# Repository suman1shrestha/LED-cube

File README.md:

# LED-cube
Led cube using 555-timer

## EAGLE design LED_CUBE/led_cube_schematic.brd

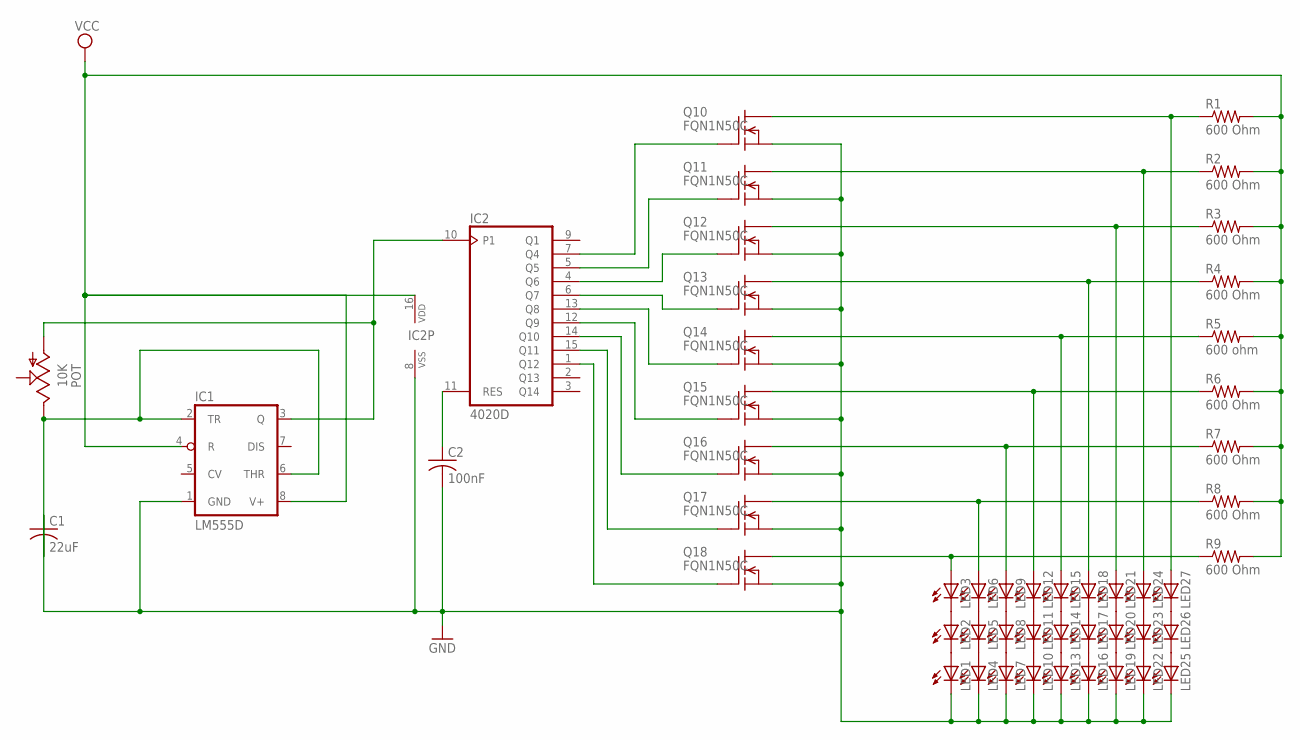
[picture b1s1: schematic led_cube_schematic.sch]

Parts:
C1: 22uF; C075-032X103
C2: 100nF; C075-032X103
IC1: LM555D; SO08
IC2: 4020D; SO16
LED1, LED2, LED3, LED4, LED5, LED6, LED7, LED8, LED9, LED10, LED11, LED12, LED13, LED14, LED15, LED16, LED17, LED18, LED19, LED20, LED21, LED22, LED23, LED24, LED25, LED26, LED27: LEDB155; Q62902-B155
POT: 10K; LI15
Q10, Q11, Q12, Q13, Q14, Q15, Q16, Q17, Q18: FQN1N50C; TO92
R1, R2, R3, R4, R6, R7, R8, R9: 600 Ohm; 0309/12
R5: 600 ohm; 0309/12

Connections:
GND: C1.1, C2.2, IC1.1 (GND), IC2.8 (VSS), LED1.K (C), LED4.K (C), LED7.K (C), LED10.K (C), LED13.K (C), LED16.K (C), LED19.K (C), LED22.K (C), LED25.K (C), Q10.3 (S), Q11.3 (S), Q12.3 (S), Q13.3 (S), Q14.3 (S), Q15.3 (S), Q16.3 (S), Q17.3 (S), Q18.3 (S)
unnamed: C1.2, IC1.2 (TR), IC1.6 (THR), POT.E
unnamed: IC2.1 (Q12), Q18.1 (G)
unnamed: IC1.3 (Q), IC2.10 (P1), POT.A
unnamed: IC2.15 (Q11), Q17.1 (G)
unnamed: C2.1, IC2.11 (RES)
unnamed: IC2.14 (Q10), Q16.1 (G)
unnamed: IC2.12 (Q9), Q15.1 (G)
unnamed: IC2.13 (Q8), Q14.1 (G)
unnamed: IC2.6 (Q7), Q13.1 (G)
unnamed: IC2.4 (Q6), Q12.1 (G)
unnamed: IC2.5 (Q5), Q11.1 (G)
unnamed: IC2.7 (Q4), Q10.1 (G)
unnamed: LED1.A, LED2.K (C)
unnamed: LED2.A, LED3.K (C)
unnamed: LED4.A, LED5.K (C)
unnamed: LED5.A, LED6.K (C)
unnamed: LED7.A, LED8.K (C)
unnamed: LED8.A, LED9.K (C)
unnamed: LED10.A, LED11.K (C)
unnamed: LED11.A, LED12.K (C)
unnamed: LED13.A, LED14.K (C)
unnamed: LED14.A, LED15.K (C)
unnamed: LED16.A, LED17.K (C)
unnamed: LED17.A, LED18.K (C)
unnamed: LED19.A, LED20.K (C)
unnamed: LED20.A, LED21.K (C)
unnamed: LED22.A, LED23.K (C)
unnamed: LED23.A, LED24.K (C)
unnamed: LED25.A, LED26.K (C)
unnamed: LED26.A, LED27.K (C)
unnamed: LED3.A, Q18.2 (D), R9.1
unnamed: LED6.A, Q17.2 (D), R8.1
unnamed: LED9.A, Q16.2 (D), R7.1
unnamed: LED12.A, Q15.2 (D), R6.1
unnamed: LED15.A, Q14.2 (D), R5.1
unnamed: LED18.A, Q13.2 (D), R4.1
unnamed: LED21.A, Q12.2 (D), R3.1
unnamed: LED24.A, Q11.2 (D), R2.1
unnamed: LED27.A, Q10.2 (D), R1.1
unnamed: R1.2, R2.2, R3.2, R4.2, R5.2, R6.2, R7.2, R8.2, R9.2
VCC: IC1.4 (R), IC1.8 (V+), IC2.16 (VDD)

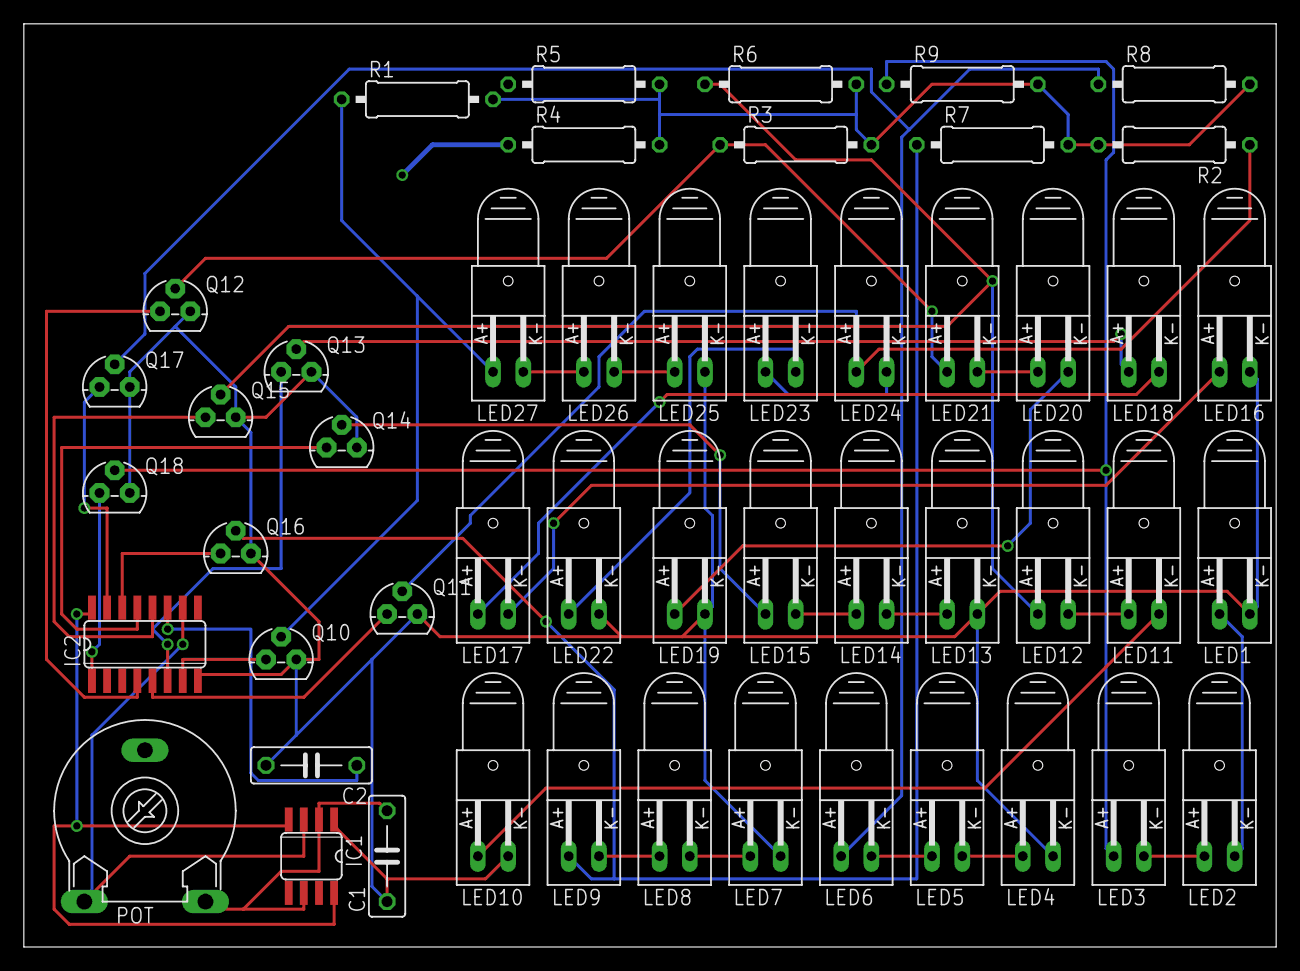
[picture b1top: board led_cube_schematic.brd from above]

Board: 2 copper layers, 105.1 x 77.5 mm, 50 parts (0 on the bottom side), 42 nets.

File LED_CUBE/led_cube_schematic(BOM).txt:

Partlist exported from /Users/sumanshrestha/Dropbox/uta/cse3323/LED_CUBE/led_cube_schematic.sch at 12/14/16 8:09 PM

Part  Value    Device          Package      Description                                      
C1    22uF     C-US075-032X103 C075-032X103 CAPACITOR, American symbol                       
C2    100nF    C-US075-032X103 C075-032X103 CAPACITOR, American symbol                       
IC1   LM555D   LM555D          SO08         TIMER                                            
IC2   4020D    4020D           SO16         14-stage binary/ripple COUNTER                   
LED1           LEDB155         Q62902-B155  LED                                              
LED2           LEDB155         Q62902-B155  LED                                              
LED3           LEDB155         Q62902-B155  LED                                              
LED4           LEDB155         Q62902-B155  LED                                              
LED5           LEDB155         Q62902-B155  LED                                              
LED6           LEDB155         Q62902-B155  LED                                              
LED7           LEDB155         Q62902-B155  LED                                              
LED8           LEDB155         Q62902-B155  LED                                              
LED9           LEDB155         Q62902-B155  LED                                              
LED10          LEDB155         Q62902-B155  LED                                              
LED11          LEDB155         Q62902-B155  LED                                              
LED12          LEDB155         Q62902-B155  LED                                              
LED13          LEDB155         Q62902-B155  LED                                              
LED14          LEDB155         Q62902-B155  LED                                              
LED15          LEDB155         Q62902-B155  LED                                              
LED16          LEDB155         Q62902-B155  LED                                              
LED17          LEDB155         Q62902-B155  LED                                              
LED18          LEDB155         Q62902-B155  LED                                              
LED19          LEDB155         Q62902-B155  LED                                              
LED20          LEDB155         Q62902-B155  LED                                              
LED21          LEDB155         Q62902-B155  LED                                              
LED22          LEDB155         Q62902-B155  LED                                              
LED23          LEDB155         Q62902-B155  LED                                              
LED24          LEDB155         Q62902-B155  LED                                              
LED25          LEDB155         Q62902-B155  LED                                              
LED26          LEDB155         Q62902-B155  LED                                              
LED27          LEDB155         Q62902-B155  LED                                              
POT   10K      TRIM_US-LI15    LI15         POTENTIOMETER                                    
Q10   FQN1N50C FQN1N50C        TO92         N-Channel Enhancement MOSFET 500V, 0.4A, 6.0 Ohm 
Q11   FQN1N50C FQN1N50C        TO92         N-Channel Enhancement MOSFET 500V, 0.4A, 6.0 Ohm 
Q12   FQN1N50C FQN1N50C        TO92         N-Channel Enhancement MOSFET 500V, 0.4A, 6.0 Ohm 
Q13   FQN1N50C FQN1N50C        TO92         N-Channel Enhancement MOSFET 500V, 0.4A, 6.0 Ohm 
Q14   FQN1N50C FQN1N50C        TO92         N-Channel Enhancement MOSFET 500V, 0.4A, 6.0 Ohm 
Q15   FQN1N50C FQN1N50C        TO92         N-Channel Enhancement MOSFET 500V, 0.4A, 6.0 Ohm 
Q16   FQN1N50C FQN1N50C        TO92         N-Channel Enhancement MOSFET 500V, 0.4A, 6.0 Ohm 
Q17   FQN1N50C FQN1N50C        TO92         N-Channel Enhancement MOSFET 500V, 0.4A, 6.0 Ohm 
Q18   FQN1N50C FQN1N50C        TO92         N-Channel Enhancement MOSFET 500V, 0.4A, 6.0 Ohm 
R1    600 Ohm  R-US_0309/12    0309/12      RESISTOR, American symbol                        
R2    600 Ohm  R-US_0309/12    0309/12      RESISTOR, American symbol                        
R3    600 Ohm  R-US_0309/12    0309/12      RESISTOR, American symbol                        
R4    600 Ohm  R-US_0309/12    0309/12      RESISTOR, American symbol                        
R5    600 ohm  R-US_0309/12    0309/12      RESISTOR, American symbol                        
R6    600 Ohm  R-US_0309/12    0309/12      RESISTOR, American symbol                        
R7    600 Ohm  R-US_0309/12    0309/12      RESISTOR, American symbol                        
R8    600 Ohm  R-US_0309/12    0309/12      RESISTOR, American symbol                        
R9    600 Ohm  R-US_0309/12    0309/12      RESISTOR, American symbol
